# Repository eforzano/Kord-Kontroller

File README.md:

# Kord Kontroller
The Kord Kontroller is a MIDI controller that maps common chordal relationships in Western music theory. This pattern mapping allows you to play major, minor, and other common chords in the same pattern regardless of the key! The newest design is focusing on an ergonomic design based on your hand. For more information check out the [Hackaday page](https://hackaday.io/project/161105-kord-kontroller). 

## Theory  
The Kord Kontroller is a musical interface that maps the notes in the same pattern rather than being forced to memorize patterns that are caused by restrictions of acoustical phenomena (i.e. strings and metal). The advantage of being able to map the buttons in an intuitive way encourages music creation and lowers the threshold of learning music. The Kord Kontroller is laid out into two sections: the key selector area and tonal selector area. 

The three type of key selectors are a piano key selector, a circle of fifths key selector, and an isomorphic key selector. Once you select a note on the key selector, for example a C, this maps the tonal selectors in a consistent pattern regardless of the key. The tonal selectors are mapped to the 1 3 5 7 9 11 13 (C E G B D F A) of the key selected like below: 

```
3  5  7  9  11  13

1  
```

The 1 (or the root) and these corresponding notes are selected because they are really common chordal relationships. The 1 is mapped topographically lower on the controller in order to match your hand lay out and since it is commonly played with your thumb. This allows you to play major chords and other common chords in the same pattern regardless of the key!

We did not want to only let you play major chords so we added the flat and sharp equivalent rows: b3 b5 b7 b9 b11 b13 and #3 #5 #7 #9 #11 #13. (Note: we understand that it is not common to refer to the 4 as a #3 or the 8 as #7, but this is more to emphasize the relationships). This allows one to play minor chords and other chords in the exact same way as well. We also added some other common notes like the 2 b2 12 14 etc. We also added octave buttons and mode changes to switch the key selectors. This ended up with this final layout:
```
                       12    14
      4  #5   8   #9  #11   b14

2     3    5   7    9  11    13

b2    b3   b5  b7   b9 10   b13

1               6           #12

```

For any questions or comments email: eforzano at gmail.com

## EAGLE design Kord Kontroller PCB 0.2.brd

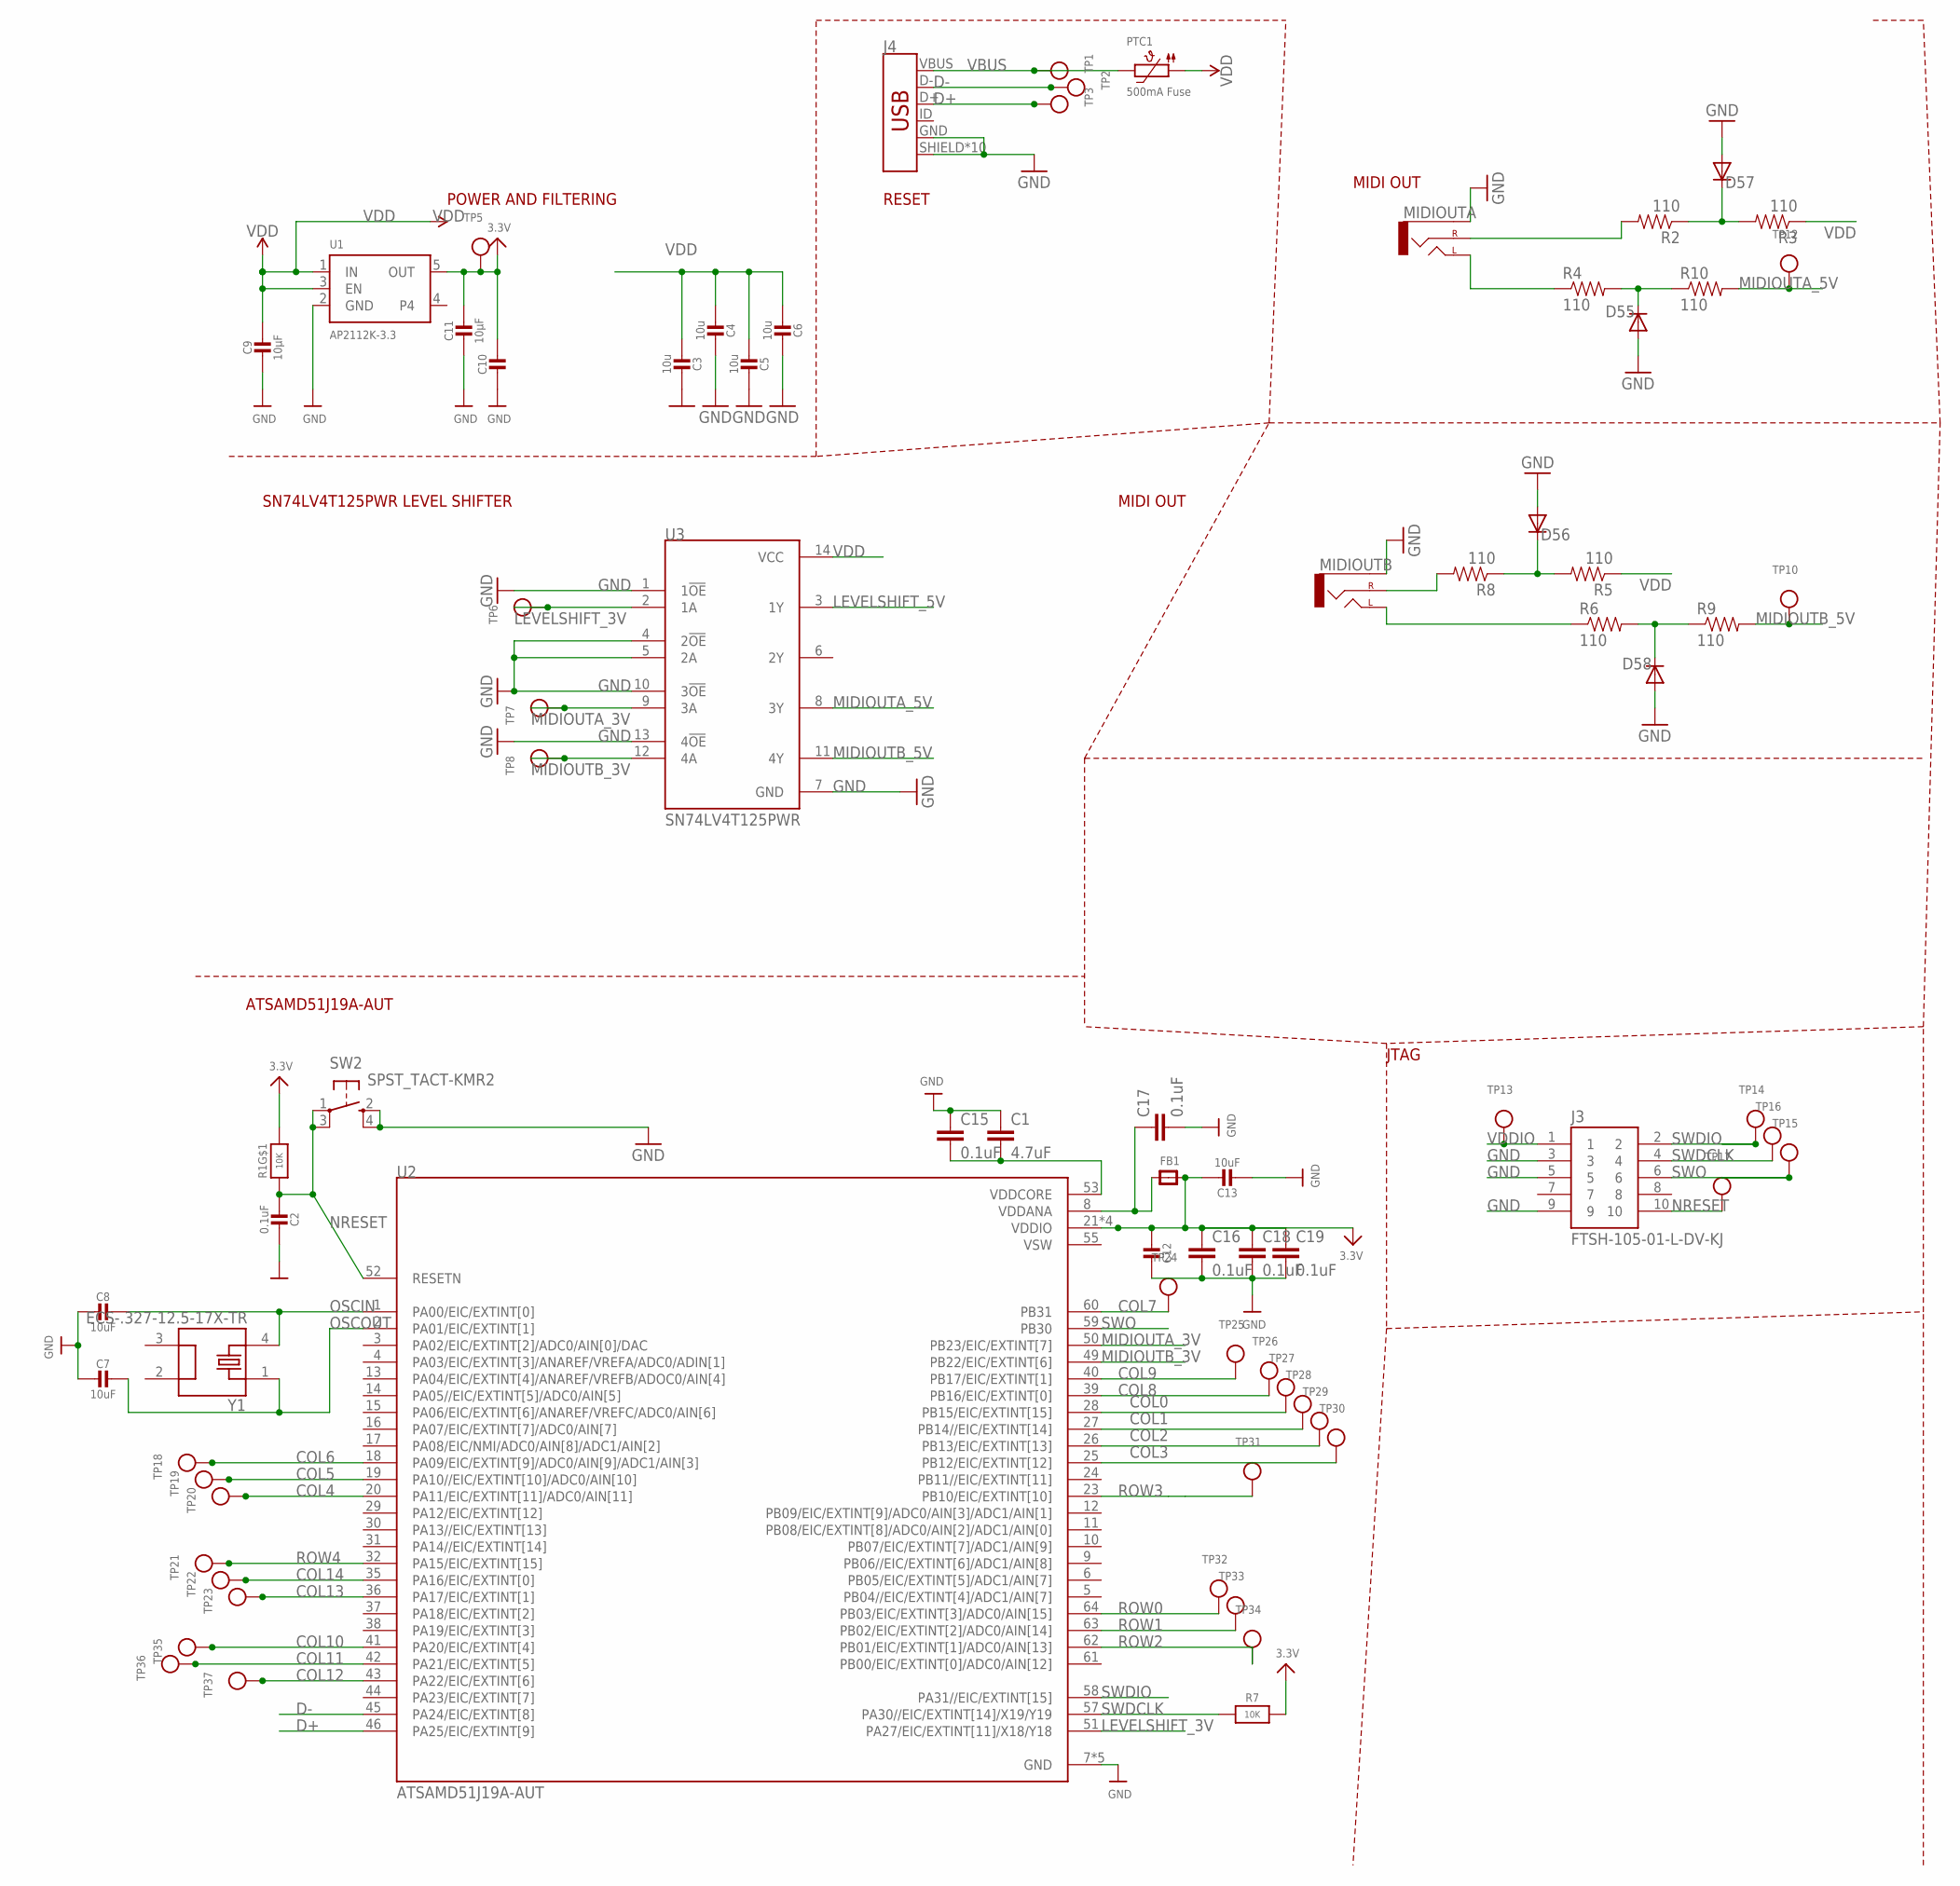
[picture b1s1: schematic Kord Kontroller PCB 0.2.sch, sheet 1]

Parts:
C1: 4.7uF; 0603
C2: 0.1uF; 0603-NO
C3, C4, C5, C6: 10u; 0805-NO
C7, C8, C13: 10uF; 0805-NO
C9, C11: 10µF; 0805-NO
C10, C12: 1uF; 0603-NO
C15, C16, C17, C18, C19: 0.1uF; 0603
D55, D56, D57, D58: DIODE-SOD123; SOD123
FB1: FERRITE; 0603
J3: FTSH-105-01-L-DV-KJ; SAMTEC_FTSH-105-01-L-DV-K
J4: USB_MICRO-B_HALF_PTH_MILL; USB-MICROB-PTH-MILL
MIDIOUTA: AUDIO_JACK_2.5MM_2.5MM_SMD; STEREOJACK2.5MM
MIDIOUTB: AUDIO_JACK_2.5MM_2.5MM_SMD; STEREOJACK2.5MM
PTC1: 500mA Fuse; 1206
R1: 10K; RESPACK_4X0603
R2, R3, R4, R5, R6, R8, R9, R10: 110; 0603-RES
R7: 10K; 0603-NO
SW2: SPST_TACT-KMR2; KMR2
TP1, TP2, TP3, TP5, TP6, TP7, TP8, TP10, TP12, TP13, TP14, TP15, TP16, TP17, TP18, TP19, TP20, TP21, TP22, TP23, TP24, TP25, TP26, TP27, TP28, TP29, TP30, TP31, TP32, TP33, TP34, TP35, TP36, TP37: TESTPOINTROUND1MM; TESTPOINT_ROUND_1MM
U1: AP2112K-3.3; SOT23-5
U2: ATSAMD51J19A-AUT; QFP50P1200X1200X120-64N
U3: SN74LV4T125PWR; SOP65P640X120-14N
Y1: ECS-.327-12.5-17X-TR; XTAL_ECS-.327-12.5-17X-TR

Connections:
COL0: TP27.P$1, U2.28 (PB15/EIC/EXTINT[15]); also elsewhere on the board
COL1: TP28.P$1, U2.27 (PB14//EIC/EXTINT[14]); also elsewhere on the board
COL2: TP29.P$1, U2.26 (PB13/EIC/EXTINT[13]); also elsewhere on the board
COL3: TP30.P$1, U2.25 (PB12/EIC/EXTINT[12]); also elsewhere on the board
COL4: TP20.P$1, U2.20 (PA11/EIC/EXTINT[11]/ADC0/AIN[11]); also elsewhere on the board
COL5: TP19.P$1, U2.19 (PA10//EIC/EXTINT[10]/ADC0/AIN[10]); also elsewhere on the board
COL6: TP18.P$1, U2.18 (PA09/EIC/EXTINT[9]/ADC0/AIN[9]/ADC1/AIN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); also elsewhere on the board
COL7: TP24.P$1, U2.60 (PB31); also elsewhere on the board
COL8: TP26.P$1, U2.39 (PB16/EIC/EXTINT[0]); also elsewhere on the board
COL9: TP25.P$1, U2.40 (PB17/EIC/EXTINT[1]); also elsewhere on the board
COL10: TP35.P$1, U2.41 (PA20/EIC/EXTINT[4]); also elsewhere on the board
COL11: TP36.P$1, U2.42 (PA21/EIC/EXTINT[5]); also elsewhere on the board
COL12: TP37.P$1, U2.43 (PA22/EIC/EXTINT[6]); also elsewhere on the board
COL13: TP23.P$1, U2.36 (PA17/EIC/EXTINT[1]); also elsewhere on the board
COL14: TP22.P$1, U2.35 (PA16/EIC/EXTINT[0]); also elsewhere on the board
D+: J4.D+, TP3.P$1, U2.46 (PA25/EIC/EXTINT[9])
D-: J4.D-, TP2.P$1, U2.45 (PA24/EIC/EXTINT[8])
GND: C1.1, C2.1, C3.1, C4.1, C5.1, C6.1, C7.2, C8.2, C9.2, C10.2, C11.2, C12.1, C13.2, C15.1, C16.2, C17.2, C18.2, C19.2, D55.A, D56.A, D57.A, D58.A, J3.3, J3.5, J3.9, J4.GND, J4.SHIELD, J4.SHIELD2 (SHIELD), J4.SHIELD3 (SHIELD), J4.SHIELD4 (SHIELD), J4.SHIELD5 (SHIELD), J4.SHIELD6 (SHIELD), J4.SHIELD7 (SHIELD), J4.SHIELD8 (SHIELD), J4.SHIELD9 (SHIELD), J4.SHIELD10 (SHIELD), MIDIOUTA.5 (SLEEVE), MIDIOUTB.5 (SLEEVE), SW2.2 (S), SW2.4 (S1), U1.2 (GND), U2.7 (GND), U2.22 (GND), U2.33 (GND), U2.47 (GND), U2.54 (GND), U3.1 (1!OE), U3.4 (2!OE), U3.5 (2A), U3.7 (GND), U3.10 (3!OE), U3.13 (4!OE); also elsewhere on the board
LEVELSHIFT_3V: TP6.P$1, U2.51 (PA27/EIC/EXTINT[11]/X18/Y18), U3.2 (1A)
LEVELSHIFT_5V: U3.3 (1Y); also elsewhere on the board
MIDIOUTA_3V: TP7.P$1, U2.50 (PB23/EIC/EXTINT[7]), U3.9 (3A)
MIDIOUTA_5V: R10.2, TP12.P$1, U3.8 (3Y)
MIDIOUTB_3V: TP8.P$1, U2.49 (PB22/EIC/EXTINT[6]), U3.12 (4A)
MIDIOUTB_5V: R9.2, TP10.P$1, U3.11 (4Y)
unnamed: MIDIOUTB.1 (LEFT), R6.1
unnamed: D58.C, R6.2, R9.1
unnamed: D57.C, R2.1, R3.2
unnamed: MIDIOUTA.4 (RIGHT), R2.2
unnamed: D55.C, R4.2, R10.1
unnamed: D56.C, R5.2, R8.1
unnamed: MIDIOUTB.4 (RIGHT), R8.2
unnamed: MIDIOUTA.1 (LEFT), R4.1
NRESET: C2.2, J3.10, R1.1, SW2.1, SW2.3 (P1), TP17.P$1, U2.52 (RESETN)
OSCIN: C8.1, U2.1 (PA00/EIC/EXTINT[0]), Y1.4
OSCOUT: C7.1, U2.2 (PA01/EIC/EXTINT[1]), Y1.1
ROW0: TP32.P$1, U2.64 (PB03/EIC/EXTINT[3]/ADC0/AIN[15]); also elsewhere on the board
ROW1: TP33.P$1, U2.63 (PB02/EIC/EXTINT[2]/ADC0/AIN[14]); also elsewhere on the board
ROW2: TP34.P$1, U2.62 (PB01/EIC/EXTINT[1]/ADC0/AIN[13]); also elsewhere on the board
ROW3: TP31.P$1, U2.23 (PB10/EIC/EXTINT[10]); also elsewhere on the board
ROW4: TP21.P$1, U2.32 (PA15/EIC/EXTINT[15]); also elsewhere on the board
SWDCLK: J3.4, R7.1, TP16.P$1, U2.57 (PA30//EIC/EXTINT[14]/X19/Y19)
SWDIO: J3.2, TP14.P$1, U2.58 (PA31//EIC/EXTINT[15])
SWO: J3.6, TP15.P$1, U2.59 (PB30)
VBUS: J4.VBUS, PTC1.2, TP1.P$1
VDD: C3.2, C4.2, C5.2, C6.2, C9.1, PTC1.1, R3.1, R5.1, U1.1 (IN), U1.3 (EN), U3.14 (VCC); also elsewhere on the board
VDDANA: C17.1, FB1.1, U2.8 (VDDANA)
VDDCORE1: C1.2, C15.2, U2.53 (VDDCORE)
VDDIO: C10.1, C11.1, C12.2, C13.1, C16.1, C18.1, C19.1, FB1.2, J3.1, R1.8 (2), R7.2, TP5.P$1, TP13.P$1, U1.5 (OUT), U2.21 (VDDIO), U2.34 (VDDIO), U2.48 (VDDIO), U2.56 (VDDIO)
VSW: U2.55 (VSW)

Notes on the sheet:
POWER AND FILTERING
RESET
MIDI OUT
SN74LV4T125PWR LEVEL SHIFTER
JTAG
ATSAMD51J19A-AUT

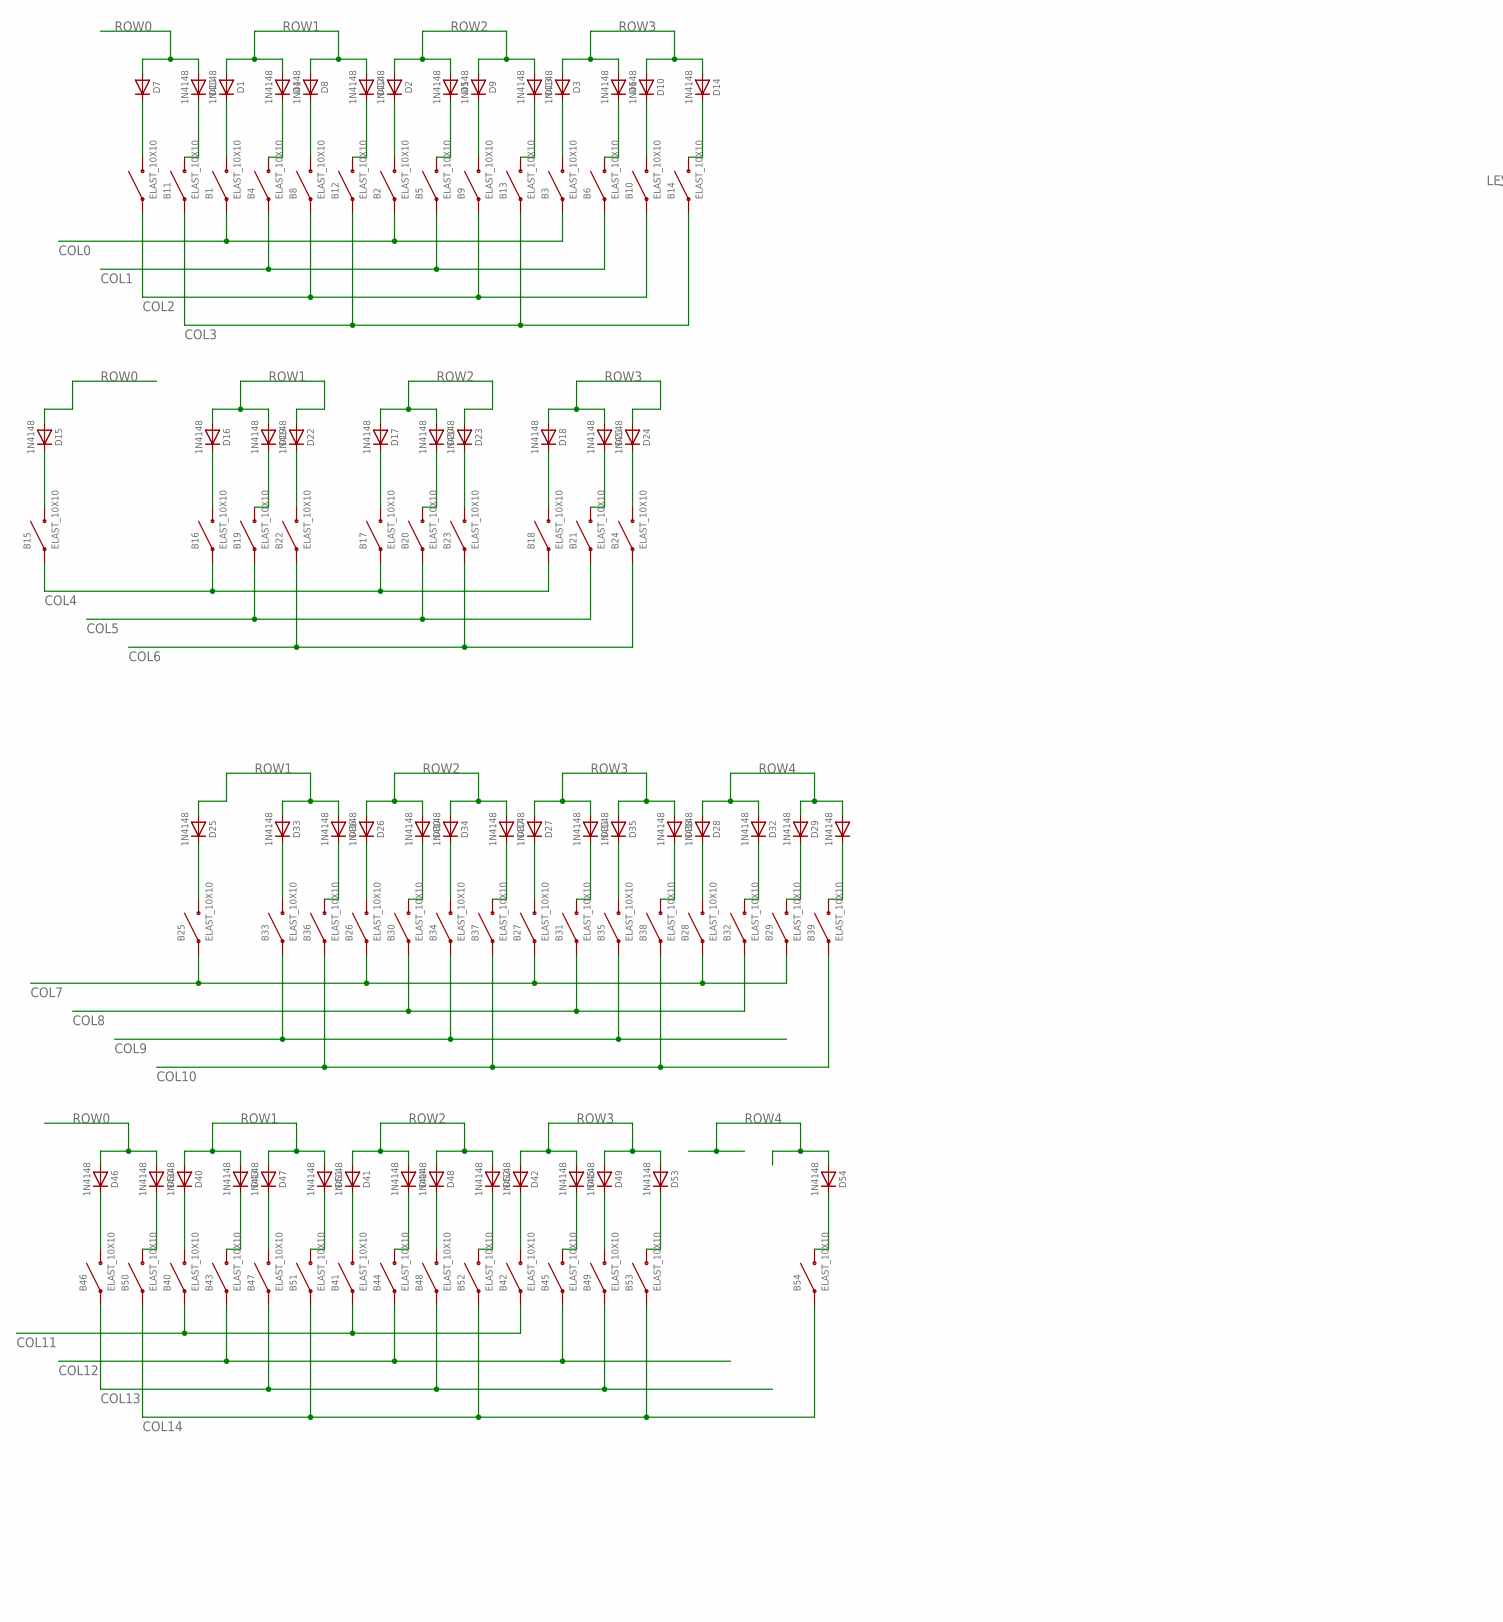
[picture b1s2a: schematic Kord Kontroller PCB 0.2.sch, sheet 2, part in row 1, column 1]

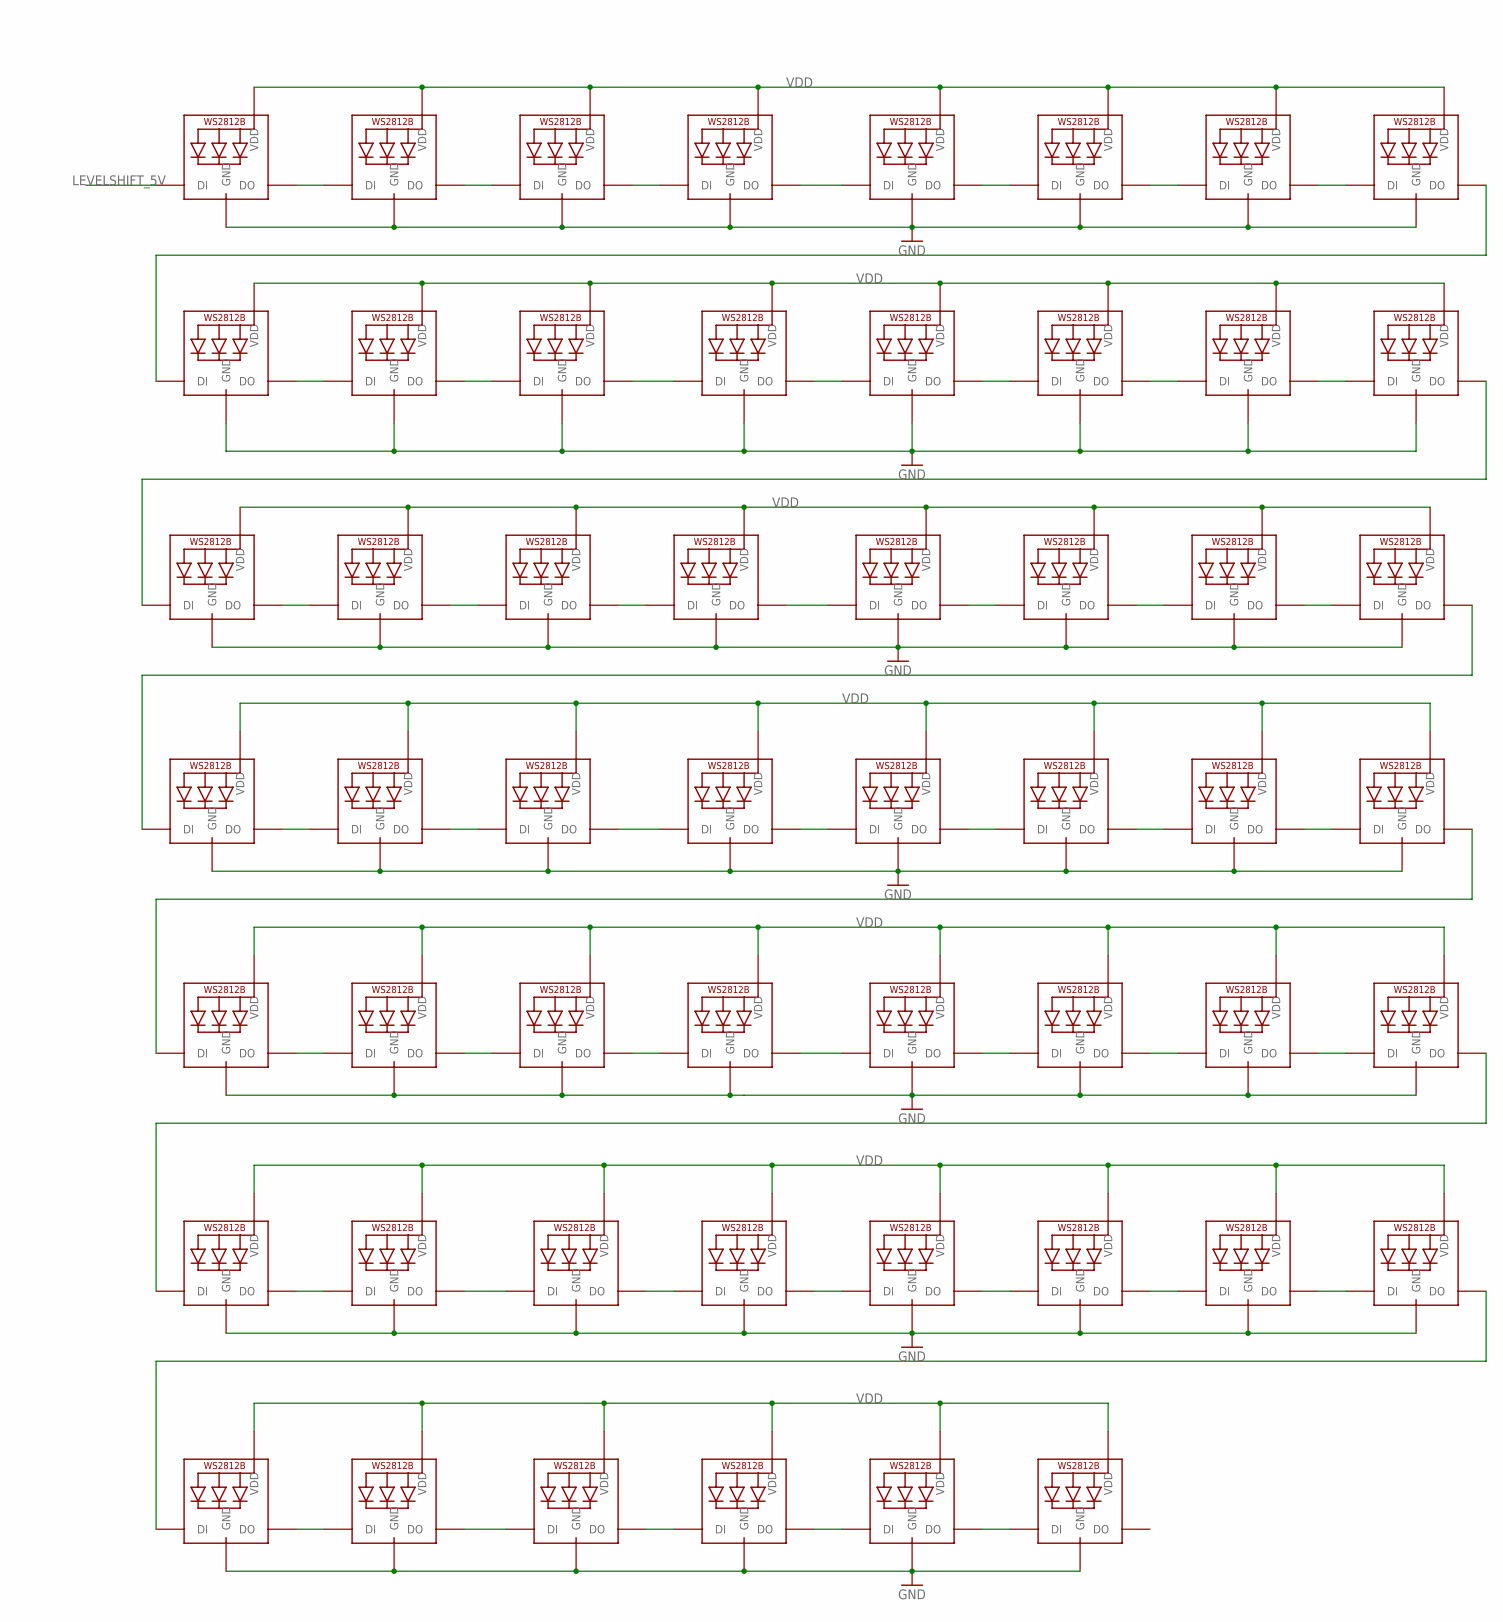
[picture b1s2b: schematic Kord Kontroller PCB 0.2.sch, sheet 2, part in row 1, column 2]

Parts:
B1, B2, B3, B4, B5, B6, B7, B8, B9, B10, B11, B12, B13, B14, B15, B16, B17, B18, B19, B20, B21, B22, B23, B24, B25, B26, B27, B28, B29, B30, B31, B32, B33, B34, B35, B36, B37, B38, B39, B40, B41, B42, B43, B44, B45, B46, B47, B48, B49, B50, B51, B52, B53, B54: ELAST_10X10; ELAST_PAD_SQUARE_10MM_4X4WIDE
D1, D2, D3, D4, D5, D6, D7, D8, D9, D10, D11, D12, D13, D14, D15, D16, D17, D18, D19, D20, D21, D22, D23, D24, D25, D26, D27, D28, D29, D30, D31, D32, D33, D34, D35, D36, D37, D38, D39, D40, D41, D42, D43, D44, D45, D46, D47, D48, D49, D50, D51, D52, D53, D54: 1N4148; SOD-323
LED1, LED2, LED3, LED4, LED5, LED6, LED7, LED8, LED9, LED10, LED11, LED12, LED13, LED14, LED15, LED16, LED17, LED18, LED19, LED20, LED21, LED22, LED23, LED24, LED25, LED26, LED27, LED28, LED29, LED30, LED31, LED32, LED33, LED34, LED35, LED36, LED37, LED38, LED39, LED40, LED41, LED42, LED43, LED44, LED45, LED46, LED47, LED48, LED49, LED50, LED51, LED52, LED53, LED54: WS2812BHRGB32M; LED3535

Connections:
COL0: B1.P$1, B2.P$1, B3.P$1; also elsewhere on the board
COL1: B4.P$1, B5.P$1, B6.P$1; also elsewhere on the board
COL2: B7.P$1, B8.P$1, B9.P$1, B10.P$1; also elsewhere on the board
COL3: B11.P$1, B12.P$1, B13.P$1, B14.P$1; also elsewhere on the board
COL4: B15.P$1, B16.P$1, B17.P$1, B18.P$1; also elsewhere on the board
COL5: B19.P$1, B20.P$1, B21.P$1; also elsewhere on the board
COL6: B22.P$1, B23.P$1, B24.P$1; also elsewhere on the board
COL7: B25.P$1, B26.P$1, B27.P$1, B28.P$1, B29.P$1; also elsewhere on the board
COL8: B30.P$1, B31.P$1, B32.P$1; also elsewhere on the board
COL9: B33.P$1, B34.P$1, B35.P$1; also elsewhere on the board
COL10: B36.P$1, B37.P$1, B38.P$1, B39.P$1; also elsewhere on the board
COL11: B40.P$1, B41.P$1, B42.P$1; also elsewhere on the board
COL12: B43.P$1, B44.P$1, B45.P$1; also elsewhere on the board
COL13: B46.P$1, B47.P$1, B48.P$1, B49.P$1; also elsewhere on the board
COL14: B50.P$1, B51.P$1, B52.P$1, B53.P$1, B54.P$1; also elsewhere on the board
GND: LED1.3 (GND), LED2.3 (GND), LED3.3 (GND), LED4.3 (GND), LED5.3 (GND), LED6.3 (GND), LED7.3 (GND), LED8.3 (GND), LED9.3 (GND), LED10.3 (GND), LED11.3 (GND), LED12.3 (GND), LED13.3 (GND), LED14.3 (GND), LED15.3 (GND), LED16.3 (GND), LED17.3 (GND), LED18.3 (GND), LED19.3 (GND), LED20.3 (GND), LED21.3 (GND), LED22.3 (GND), LED23.3 (GND), LED24.3 (GND), LED25.3 (GND), LED26.3 (GND), LED27.3 (GND), LED28.3 (GND), LED29.3 (GND), LED30.3 (GND), LED31.3 (GND), LED32.3 (GND), LED33.3 (GND), LED34.3 (GND), LED35.3 (GND), LED36.3 (GND), LED37.3 (GND), LED38.3 (GND), LED39.3 (GND), LED40.3 (GND), LED41.3 (GND), LED42.3 (GND), LED43.3 (GND), LED44.3 (GND), LED45.3 (GND), LED46.3 (GND), LED47.3 (GND), LED48.3 (GND), LED49.3 (GND), LED50.3 (GND), LED51.3 (GND), LED52.3 (GND), LED53.3 (GND), LED54.3 (GND); also elsewhere on the board
LEVELSHIFT_5V: LED1.4 (DI); also elsewhere on the board
unnamed: LED36.2 (DO), LED37.4 (DI)
unnamed: B7.P$2, D7.C
unnamed: B11.P$2, D11.C
unnamed: B1.P$2, D1.C
unnamed: LED17.2 (DO), LED18.4 (DI)
unnamed: LED18.2 (DO), LED19.4 (DI)
unnamed: B4.P$2, D4.C
unnamed: LED19.2 (DO), LED20.4 (DI)
unnamed: LED1.2 (DO), LED2.4 (DI)
unnamed: LED2.2 (DO), LED3.4 (DI)
unnamed: LED3.2 (DO), LED4.4 (DI)
unnamed: LED4.2 (DO), LED5.4 (DI)
unnamed: B8.P$2, D8.C
unnamed: LED5.2 (DO), LED6.4 (DI)
unnamed: LED6.2 (DO), LED7.4 (DI)
unnamed: B12.P$2, D12.C
unnamed: LED7.2 (DO), LED8.4 (DI)
unnamed: B2.P$2, D2.C
unnamed: LED8.2 (DO), LED9.4 (DI)
unnamed: B5.P$2, D5.C
unnamed: B9.P$2, D9.C
unnamed: B13.P$2, D13.C
unnamed: B3.P$2, D3.C
unnamed: B6.P$2, D6.C
unnamed: B10.P$2, D10.C
unnamed: B14.P$2, D14.C
unnamed: LED9.2 (DO), LED10.4 (DI)
unnamed: LED10.2 (DO), LED11.4 (DI)
unnamed: LED11.2 (DO), LED12.4 (DI)
unnamed: LED12.2 (DO), LED13.4 (DI)
unnamed: LED13.2 (DO), LED14.4 (DI)
unnamed: LED14.2 (DO), LED15.4 (DI)
unnamed: LED15.2 (DO), LED16.4 (DI)
unnamed: LED20.2 (DO), LED21.4 (DI)
unnamed: LED21.2 (DO), LED22.4 (DI)
unnamed: LED22.2 (DO), LED23.4 (DI)
unnamed: LED23.2 (DO), LED24.4 (DI)
unnamed: LED24.2 (DO), LED25.4 (DI)
unnamed: LED25.2 (DO), LED26.4 (DI)
unnamed: LED26.2 (DO), LED27.4 (DI)
unnamed: LED28.2 (DO), LED29.4 (DI)
unnamed: LED27.2 (DO), LED28.4 (DI)
unnamed: LED29.2 (DO), LED30.4 (DI)
unnamed: LED30.2 (DO), LED31.4 (DI)
unnamed: LED31.2 (DO), LED32.4 (DI)
unnamed: B15.P$2, D15.C
unnamed: LED34.2 (DO), LED35.4 (DI)
unnamed: LED35.2 (DO), LED36.4 (DI)
unnamed: LED44.2 (DO), LED45.4 (DI)
unnamed: B16.P$2, D16.C
unnamed: B19.P$2, D19.C
unnamed: B22.P$2, D22.C
unnamed: LED43.2 (DO), LED44.4 (DI)
unnamed: B17.P$2, D17.C
unnamed: B20.P$2, D20.C
unnamed: B23.P$2, D23.C
unnamed: LED42.2 (DO), LED43.4 (DI)
unnamed: B18.P$2, D18.C
unnamed: B21.P$2, D21.C
unnamed: B24.P$2, D24.C
unnamed: LED16.2 (DO), LED17.4 (DI)
unnamed: LED50.2 (DO), LED51.4 (DI)
unnamed: LED51.2 (DO), LED52.4 (DI)
unnamed: LED52.2 (DO), LED53.4 (DI)
unnamed: B29.P$2, D29.C
unnamed: B25.P$2, D25.C
unnamed: B33.P$2, D33.C
unnamed: B36.P$2, D36.C
unnamed: B26.P$2, D26.C
unnamed: B30.P$2, D30.C
unnamed: B34.P$2, D34.C
unnamed: B37.P$2, D37.C
unnamed: B27.P$2, D27.C
unnamed: B31.P$2, D31.C
unnamed: B35.P$2, D35.C
unnamed: B38.P$2, D38.C
unnamed: LED33.2 (DO), LED34.4 (DI)
unnamed: LED37.2 (DO), LED38.4 (DI)
unnamed: LED38.2 (DO), LED39.4 (DI)
unnamed: LED39.2 (DO), LED40.4 (DI)
unnamed: LED41.2 (DO), LED42.4 (DI)
unnamed: LED45.2 (DO), LED46.4 (DI)
unnamed: LED46.2 (DO), LED47.4 (DI)
unnamed: LED47.2 (DO), LED48.4 (DI)
unnamed: LED49.2 (DO), LED50.4 (DI)
unnamed: LED53.2 (DO), LED54.4 (DI)
unnamed: LED40.2 (DO), LED41.4 (DI)
unnamed: LED48.2 (DO), LED49.4 (DI)
unnamed: LED32.2 (DO), LED33.4 (DI)
unnamed: B46.P$2, D46.C
unnamed: B50.P$2, D50.C
unnamed: B40.P$2, D40.C
unnamed: B43.P$2, D43.C
unnamed: B47.P$2, D47.C
unnamed: B51.P$2, D51.C
unnamed: B41.P$2, D41.C
unnamed: B44.P$2, D44.C
unnamed: B48.P$2, D48.C
unnamed: B52.P$2, D52.C
unnamed: B42.P$2, D42.C
unnamed: B45.P$2, D45.C
unnamed: B49.P$2, D49.C
unnamed: B53.P$2, D53.C
unnamed: B28.P$2, D28.C
unnamed: B32.P$2, D32.C
unnamed: B39.P$2, D39.C
unnamed: B54.P$2, D54.C
ROW0: D7.A, D11.A, D15.A, D46.A, D50.A; also elsewhere on the board
ROW1: D1.A, D4.A, D8.A, D12.A, D16.A, D19.A, D22.A, D25.A, D33.A, D36.A, D40.A, D43.A, D47.A, D51.A; also elsewhere on the board
ROW2: D2.A, D5.A, D9.A, D13.A, D17.A, D20.A, D23.A, D26.A, D30.A, D34.A, D37.A, D41.A, D44.A, D48.A, D52.A; also elsewhere on the board
ROW3: D3.A, D6.A, D10.A, D14.A, D18.A, D21.A, D24.A, D27.A, D31.A, D35.A, D38.A, D42.A, D45.A, D49.A, D53.A; also elsewhere on the board
ROW4: D28.A, D29.A, D32.A, D39.A, D54.A; also elsewhere on the board
VDD: LED1.1 (VDD), LED2.1 (VDD), LED3.1 (VDD), LED4.1 (VDD), LED5.1 (VDD), LED6.1 (VDD), LED7.1 (VDD), LED8.1 (VDD), LED9.1 (VDD), LED10.1 (VDD), LED11.1 (VDD), LED12.1 (VDD), LED13.1 (VDD), LED14.1 (VDD), LED15.1 (VDD), LED16.1 (VDD), LED17.1 (VDD), LED18.1 (VDD), LED19.1 (VDD), LED20.1 (VDD), LED21.1 (VDD), LED22.1 (VDD), LED23.1 (VDD), LED24.1 (VDD), LED25.1 (VDD), LED26.1 (VDD), LED27.1 (VDD), LED28.1 (VDD), LED29.1 (VDD), LED30.1 (VDD), LED31.1 (VDD), LED32.1 (VDD), LED33.1 (VDD), LED34.1 (VDD), LED35.1 (VDD), LED36.1 (VDD), LED37.1 (VDD), LED38.1 (VDD), LED39.1 (VDD), LED40.1 (VDD), LED41.1 (VDD), LED42.1 (VDD), LED43.1 (VDD), LED44.1 (VDD), LED45.1 (VDD), LED46.1 (VDD), LED47.1 (VDD), LED48.1 (VDD), LED49.1 (VDD), LED50.1 (VDD), LED51.1 (VDD), LED52.1 (VDD), LED53.1 (VDD), LED54.1 (VDD); also elsewhere on the board

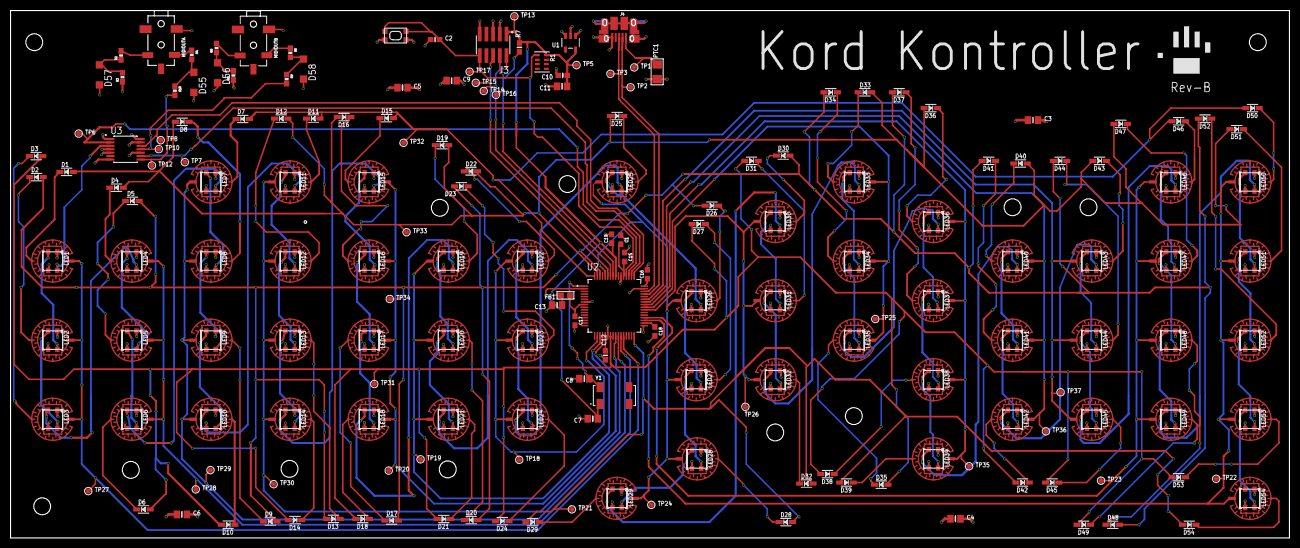
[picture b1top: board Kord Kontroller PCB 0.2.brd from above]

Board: 4 copper layers, 242.5 x 100.0 mm, 239 parts (0 on the bottom side), 155 nets.

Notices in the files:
parts and their libraries:
microbuilder: This work is placed in the public domain, and may be freely used for commercial and non-commercial work with the following conditions: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
SparkFun-Connectors: Licensing: Creative Commons ShareAlike 4.0 International - https://creativecommons.org/licenses/by-sa/4.0
